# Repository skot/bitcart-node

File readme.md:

## The bitcart
**This project is unfinished and on hold until the supply of CM4 8GB improves**

This is a Raspberry Pi CM4 carrier board optimized for being a bitcoin node.

It is heavily based on the official [Raspberry Pi CM4 Carrier Board](https://www.raspberrypi.com/products/compute-module-4-io-board/)

[Still very much WIP. The schematic is mostly done, and the PCB layout is started. Needs a lot more work, and testing!]
## features
- Uses the RPi CM4 (use the CM4108032 with 8GB RAM and 32GB eMMC storage)
- M.2 M-Key slot for NVMe SSD storage. (Need that 1TB+ for bitcoin core!)
- Powered by 20W PoE+
- Gigabit ethernet
- USB port for debugging

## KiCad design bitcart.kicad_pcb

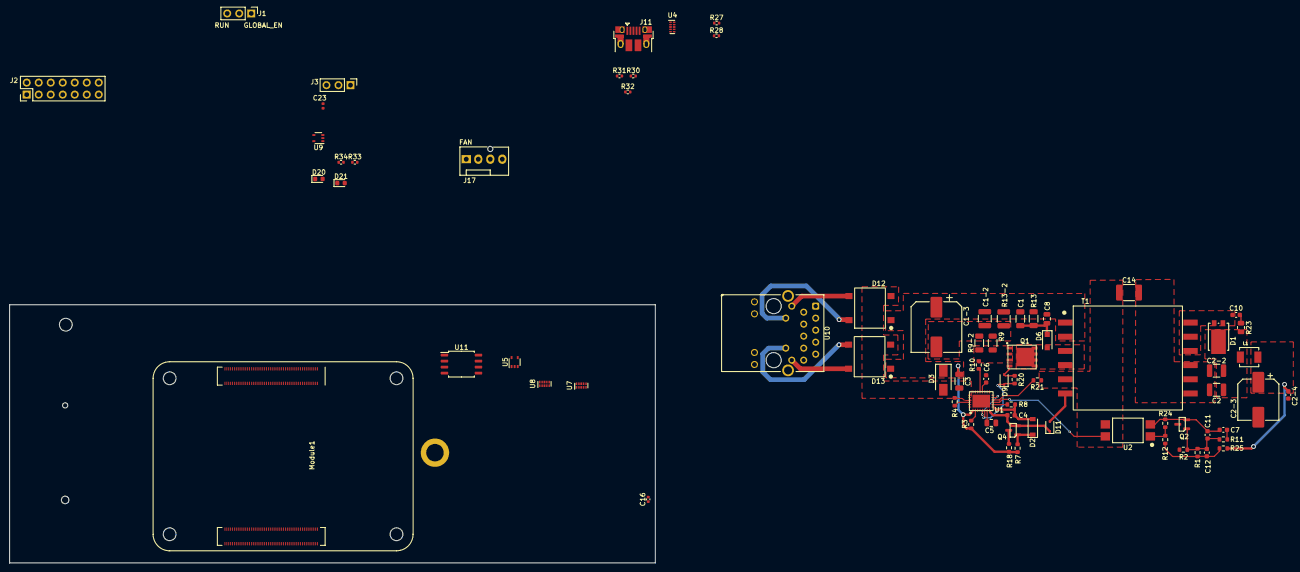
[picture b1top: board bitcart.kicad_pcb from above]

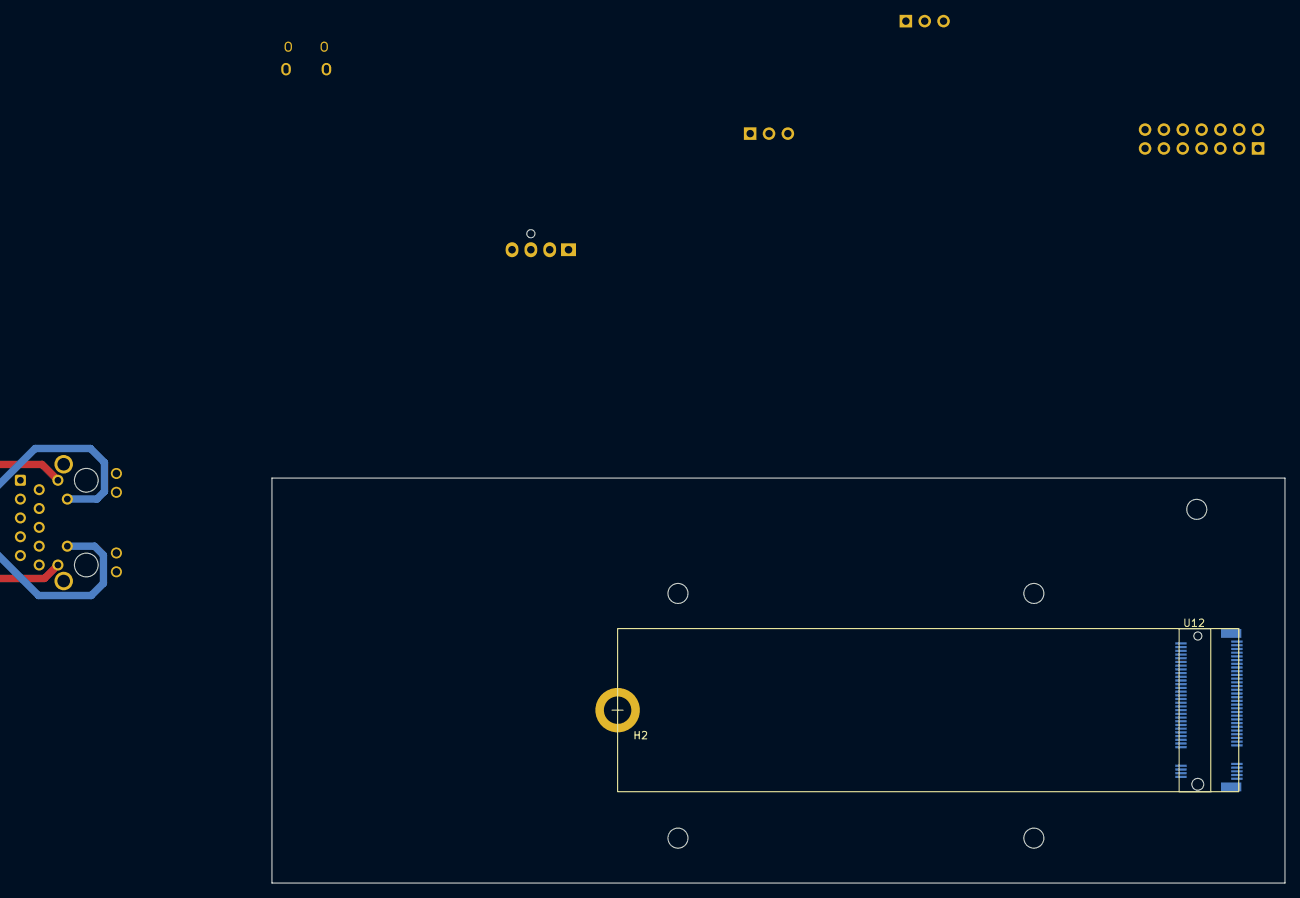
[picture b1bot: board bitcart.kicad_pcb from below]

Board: 4 copper layers, 136.6 x 54.6 mm, 78 parts (2 on the bottom side), 81 nets.

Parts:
C1, C1-2: 2.2uF; C_1210_3225Metric
C1-3: 47uF; CP_Elec_10x10.5
C2, C2-2: 22uF; C_1210_3225Metric
C2-3: 220uF; CP_Elec_8x10.5
C2-4, C7: 0.1uF; C_0603_1608Metric
C3: 0.1uF, 100V; R_1206_3216Metric
C4: 1uF; C_0603_1608Metric
C5: 4.7uF; C_0805_2012Metric
C6: 0.22uF; C_0603_1608Metric
C8: 0.1uF; C_0805_2012Metric
C10: 0.47nF; C_0603_1608Metric
C11: 220pF; C_0603_1608Metric
C12: 680pF; C_0603_1608Metric
C14: 1nF, 2000V; C_1812_4532Metric
C16, C23: 100n; C_0402_1005Metric
D1: SBR8U60P5-13
D2: 9.1V; D_SOD-123
D3: SMAJ58A; D_SMA
D6: BAV21; D_SOD-123F
D9, D11: 1N4148WS; D_SOD-323
D12, D13: DF01S
D20: LED Red; LED_0603_1608Metric
D21: LED Green; LED_0603_1608Metric
H1: MountingHole; MountingHole_2.7mm_M2.5
H2: M2.5 x 2.5mm SMD threaded standoff; 9774025151R
J1, J3: Conn_01x03; PinHeader_1x03_P2.54mm_Vertical
J2: Conn_02x07_Odd_Even; PinHeader_2x07_P2.54mm_Vertical
J11: USB_OTG; USB_Micro-B_EDAC_UCON00686
J17: Molex 470531000; FanPinHeader_1x04_P2.54mm_Vertical
L1: 0.1uH; IND_744373240010
Module1: ComputeModule4; Raspberry-Pi-4-Compute-Module
Q1: SI7430DP
Q2: TL432DBZ; SOT-23
Q4: MMBTA06LT1G; SOT-23
R1, R2: 191k; R_0603_1608Metric
R3: 24.9k; R_0603_1608Metric
R4: 28.7; R_0603_1608Metric
R7: 100k; R_0603_1608Metric
R8: 9.31k; R_0603_1608Metric
R9, R9-2: 0.082; R_1206_3216Metric
R10, R20: 4.99; R_0603_1608Metric
R11: 49.9k; R_0603_1608Metric
R12: 6.8k; R_0603_1608Metric
R13, R13-2: 20k; R_1206_3216Metric
R18: 1k; R_0603_1608Metric
R21: 10k; R_0603_1608Metric
R23: 20; R_0805_2012Metric
R24: 2k; R_0603_1608Metric
R25: 10; R_0603_1608Metric
R27, R28: 470R; R_0402_1005Metric
R30, R31: 2.2K 1%; R_0402_1005Metric
R32: 36K 1%; R_0402_1005Metric
R33, R34: 1k; R_0402_1005Metric
T1: 7491194912
U1: MP8008; QFN-28_EP_4x5_Pitch0.5mm
U2: FOD817S; SMDIP-4_W9.53mm
U4, U7, U8: TPD4EUSB30; USON-10_2.5x1.0mm_P0.5mm
U5, U9: 74LVC1G07SE-7; SOT-353_SC-70-5
U10: MagJack-A70-112-331N126; TRJG0926HENL
U11: EMC2301-1-ACZL-TR; SOIC-8_5.23x5.23mm_P1.27mm
U12: MDT320M01001

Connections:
/+3.3v: C23.1, D20.2 (A), D21.2 (A), Module1.78 (GPIO_VREF(1.8v/3.3v_Input)), Module1.84 (+3.3v_(Output)), Module1.86 (+3.3v_(Output)), R32.2, U5.5 (VCC), U11.3 (VDD)
/+5v: C2-3.1, C2-4.1, L1.2, Module1.77 (+5v_(Input)), Module1.79 (+5v_(Input)), Module1.81 (+5v_(Input)), Module1.83 (+5v_(Input)), Module1.85 (+5v_(Input)), Module1.87 (+5v_(Input)), R25.2, U9.5 (VCC)
/CM4_GPIO /+1.8v: Module1.88 (+1.8v_(Output)), Module1.90 (+1.8v_(Output))
/CM4_GPIO /AIN0: J2.5, Module1.96 (AnalogIP0)
/CM4_GPIO /AIN1: J2.6, Module1.94 (AnalogIP1)
/CM4_GPIO /BT_nDis: J3.3, Module1.91 (BT_nDisable)
/CM4_GPIO /EEPROM_nWP: J2.4, Module1.20 (EEPROM_nWP)
/CM4_GPIO /GLOBAL_EN: J1.1, J2.14, Module1.99 (Global_EN)
/CM4_GPIO /RUN_PG: J1.3, Module1.92 (RUN_PG), U9.2
/CM4_GPIO /SYNC_IN: J2.8, Module1.16 (Ethernet_SYNC_IN(1.8v))
/CM4_GPIO /SYNC_OUT: J2.9, Module1.18 (Ethernet_SYNC_OUT(1.8v))
/CM4_GPIO /TRD0_N: Module1.10 (Ethernet_Pair0_N), U8.4 (D2+), U8.7, U10.2 (TRD0-)
/CM4_GPIO /TRD0_P: Module1.12 (Ethernet_Pair0_P), U8.5 (D2-), U8.6, U10.1 (TRD0+)
/CM4_GPIO /TRD1_N: Module1.6 (Ethernet_Pair1_N), U8.2 (D1-), U8.9, U10.6 (TRD1-)
/CM4_GPIO /TRD1_P: Module1.4 (Ethernet_Pair1_P), U8.1 (D1+), U8.10, U10.3 (TRD1+)
/CM4_GPIO /TRD2_N: Module1.9 (Ethernet_Pair2_N), U7.4 (D2+), U7.7, U10.8 (TRD2-)
/CM4_GPIO /TRD2_P: Module1.11 (Ethernet_Pair2_P), U7.5 (D2-), U7.6, U10.7 (TRD2+)
/CM4_GPIO /TRD3_N: Module1.5 (Ethernet_Pair3_N), U7.2 (D1-), U7.9, U10.10 (TRD3-)
/CM4_GPIO /TRD3_P: Module1.3 (Ethernet_Pair3_P), U7.1 (D1+), U7.10, U10.9 (TRD3+)
/CM4_GPIO /WL_nDis: J3.1, Module1.89 (WL_nDisable)
/CM4_GPIO /nPWR_LED: Module1.95 (nPI_LED_PWR), U5.2
/CM4_GPIO /nRPIBOOT: J2.2, Module1.93 (nRPIBOOT)
/CM4_HighSpeed/PCIE_CLK_N: Module1.112 (PCIe_CLK_N), U12.53 (REFCLKn)
/CM4_HighSpeed/PCIE_CLK_P: Module1.110 (PCIe_CLK_P), U12.55 (REFCLKp)
/CM4_HighSpeed/PCIE_RX_N: Module1.118 (PCIe_RX_N), U12.41 (PETn0)
/CM4_HighSpeed/PCIE_RX_P: Module1.116 (PCIe_RX_P), U12.43 (PETp0)
/CM4_HighSpeed/PCIE_TX_N: Module1.124 (PCIe_TX_N), U12.47 (PERn0)
/CM4_HighSpeed/PCIE_TX_P: Module1.122 (PCIe_TX_P), U12.49 (PERp0)
/CM4_HighSpeed/PCIE_nRST: Module1.109 (PCIe_nRST), U12.50 (PREST)
/CM4_HighSpeed/USBOTG_ID: Module1.101 (USB_OTG_ID), R30.1, R31.2
/PCIe-connector/+3.3V: U12.2 (3.3V), U12.4 (3.3V), U12.12 (3.3V), U12.14 (3.3V), U12.16 (3.3V), U12.18 (3.3V), U12.70 (3.3V), U12.72 (3.3V), U12.74 (3.3V)
/PoE/+3.3v: U10.15 (LEDG_A), U10.17 (LEDY_A)
/PoE/COMP: U1.11 (COMP), U2.4
/PoE/GND1: C1.2, C1-2.2, C1-3.2, C4.2, C5.2, C6.2, C14.1, D2.2 (A), R8.1, R9.1, R9-2.1, R21.1, T1.5, U1.9 (GND), U1.20 (RTN), U1.21 (RTN), U1.29 (EP), U2.3
/PoE/ISQ: Q1.1 (S), Q1.2 (S), Q1.3 (S), R9.2, R9-2.2, R10.1
/PoE/LS: C2.1, C2-2.1, D1.1 (K), L1.1, R23.1
/PoE/NS: C10.1, D1.2 (A), D1.3 (A), T1.10, T1.11, T1.12
/PoE/TR0_TAP: D12.3, U10.11 (VC1)
/PoE/TR1_TAP: D12.4, U10.12 (VC2)
/PoE/TR2_TAP: D13.3, U10.13 (VC3)
/PoE/TR3_TAP: D13.4, U10.14 (VC4)
/PoE/VDD: C1.1, C1-2.1, C1-3.1, C3.1, C8.1, D3.1 (K), D12.1 (+), D13.1 (+), R3.2, R7.2, R13.2, R13-2.2, R18.2, T1.1, T1.2, U1.1 (AUX), U1.3 (VDD)
/PoE/VIN: C4.1, D11.1 (K), Q4.2 (E), U1.8 (VIN)
/PoE/VSS: C3.2, D3.2 (A), D12.2 (-), D13.2 (-), R4.1, U1.23 (VSS), U1.24 (VSS), U1.25 (FTY)
/PoE/W1: D6.2 (A), Q1.5 (D), T1.3, T1.4
/PoE/W2: D11.2 (A), T1.6
/PoE/W3: R12.2, R24.2, U2.1
/PoE/W4: C7.1, C11.1, Q2.2 (K), R24.1, U2.2
/USB2-HUB/USBD_N: J11.2 (D-), U4.4 (D2+), U4.7
/USB2-HUB/USBD_P: J11.3 (D+), U4.5 (D2-), U4.6
GND: C2.2, C2-2.2, C2-3.2, C2-4.2, C14.2, C16.2, C23.2, J1.2, J2.1, J2.3, J2.7, J2.10, J2.12, J3.2, J11.5 (GND), J11.6 (Shield), J17.1, Module1.1 (GND), Module1.2 (GND), Module1.7 (GND), Module1.8 (GND), Module1.13 (GND), Module1.14 (GND), Module1.22 (GND), Module1.23 (GND), Module1.32 (GND), Module1.33 (GND), Module1.42 (GND), Module1.43 (GND), Module1.52 (GND), Module1.53 (GND), Module1.59 (GND), Module1.60 (GND), Module1.65 (GND), Module1.66 (GND), Module1.71 (GND), Module1.74 (GND), Module1.98 (GND), Module1.107 (GND), Module1.108 (GND), Module1.113 (GND), Module1.114 (GND), Module1.119 (GND), Module1.120 (GND), Module1.125 (GND), Module1.126 (GND), Module1.131 (GND), Module1.132 (GND), Module1.137 (GND), Module1.138 (GND), Module1.144 (GND), Module1.150 (GND), Module1.155 (GND), Module1.156 (GND), Module1.161 (GND), Module1.162 (GND), Module1.167 (GND), Module1.168 (GND), Module1.173 (GND), Module1.174 (GND), Module1.179 (GND), Module1.180 (GND), Module1.185 (GND), Module1.186 (GND), Module1.191 (GND), Module1.192 (GND), Module1.197 (GND), Module1.198 (GND), Q2.3 (A), R2.1, R30.2, T1.7, T1.8, T1.9, U4.3 (GND), U4.8 (GND), U5.3 (GND), U7.3 (GND), U7.8 (GND), U8.3 (GND), U8.8 (GND), U9.3 (GND), U10.19 (SHIELD), U10.20 (SHIELD), U11.4 (GND), U12.1 (GND), U12.3 (GND), U12.9 (GND), U12.15 (GND), U12.21 (GND), U12.27 (GND), U12.33 (GND), U12.39 (GND), U12.45 (GND), U12.51 (GND), U12.57 (GND), U12.69 (PEDET), U12.71 (GND), U12.73 (GND), U12.75 (GND), U12.76, U12.77
unnamed: C5.1, U1.7 (VCC)
unnamed: C6.1, U1.18 (SS)
unnamed: C8.2, D6.1 (K), R13.1, R13-2.1
unnamed: C10.2, R23.2
unnamed: C11.2, C12.2, Q2.1 (REF), R1.1, R2.2, R11.1
unnamed: C12.1, R1.2, R12.1, R25.1
unnamed: C16.1, U10.4 (CT), U10.5 (CT)
unnamed: D2.1 (K), Q4.1 (B), R7.1
unnamed: D9.1 (K), R20.2, U1.6 (GATE)
unnamed: D9.2 (A), Q1.4 (G), R20.1
unnamed: D21.1 (K), R34.1
unnamed: J2.13, U9.4
unnamed: J11.1 (VBUS), R31.1
unnamed: J17.3, R32.1, U11.6 (TACH)
unnamed: J17.4, U11.5 (PWM)
unnamed: Module1.21 (PI_nLED_Activity), R34.2
unnamed: Q4.3 (C), R18.1
unnamed: R3.1, U1.2 (DET)
unnamed: R4.2, U1.26 (CLASS)
unnamed: R8.2, U1.10 (RT)
unnamed: R10.2, U1.19 (ISENSE)
unnamed: C7.2, R11.2
unnamed: R21.2, U1.12 (FB)
unnamed: R27.1, U10.16 (LEDG_K)
unnamed: R28.1, U10.18 (LEDY_K)
unnamed: D20.1 (K), R33.1
unnamed: U1.5 (PG), U1.13 (EN/SYNC)
unnamed: U4.1 (D1+), U4.10
unnamed: U4.2 (D1-), U4.9
unnamed: R33.2, U5.4

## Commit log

2022-06-02 initial import
2022-06-03 removed many unused parts
2022-06-03 added PoE schematic
2022-06-03 added M.2 m-key connector to schematic
2022-06-03 schematic cleanup
2022-06-03 ignore autosaved files
2022-06-15 removed unused components
2022-06-16 added the M.2 connector and MP8008 footprints
2022-06-16 adding PoE parts
2022-06-16 added flyback mosfet footprint
2022-06-16 added a bunch more PoE footprints
2022-06-16 yet more PoE footprints
2022-06-16 all footprints added?!
2022-06-16 changed PoE transformer to Wurth 7491194912
2022-06-17 started routing PoE
2022-06-17 update gitignore
2022-09-08 readme update
